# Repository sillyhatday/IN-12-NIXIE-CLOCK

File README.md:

# IN-12 Nixie Tube Clock

## Introduction

This clock was designed with the idea of using IN-12 Nixie Tubes as its display. The design was intended to look similar to something from the 1960s with a cyberpunk style. I'm not sure I have managed this or not. I think it is more art deco style.

This did not work out and I went for something that took inspo from the 1950s. I'd say more Fallout than cyberpunk. Maybe American diner or 50's American car. I like it.

The design is to be modular and 3D printing or machining friendly. The final build I would like making from aluminium or stainless steel.

---

## 🔷 Description

The internal electronics are mounted on two PCBs with a connecting pin header. One PCB for power supplies and main logic, the second for the displays and display driver. The choice of putting the display driver on the display PCB was to reduce the amount board to board connections.

The clock housing is keyed to the cut outs in the PCBs. It's not possible to put them in the wron gplace.

The logic board contains two power supplies. One power supply is for the display tube anodes. The second power supply provides power to the logic circuit.

A 9 - 12v DC supply was decided based on testing. The system will operate from 8 to 16v on the input. I have been running mine at 9v as that is supported by more USB C power supplies than 12v.

>[!NOTE]
>Before building, decide if you will use NiMH or Alkaline batteries for backup batteries. If using non-rechargable, do not populate R39 <br>
>I suggest using the ATmega328 over the ATmega8 for lower standby power and longer operation on backup batteries. <br>
>A description of operations can be found [HERE](ClockFunctions.md)

---

## 🫐 Progress

### 🟢 Done
- First revision of PCBs
- Working firmware with some features implemented.
- Stable high voltage power supply
- Case design first revision made
- All remaining case parts, buttons, legs, back cover.
- Updated PCB & fixed errors. Changed fuse, standby circuit, rearranged PCB.
- Added onboard USB-C 9 - 12v support.
- Finished adding firmware features, standby, battery backup, EEPROM clear.
- Porting to ATMEGA328 to use lower voltage and more efficient core, LOD 1.8v vs LOD 2.7v.
- Finishing case cosmetics.
- Digit ghosting fix. Problem in hardware somewhere.
- Standby code needs inverting for new 180v power control circuit.

### 🟡 Working On
- Power measurement testing. MCU power reduction on battery power.
- Tidying up lettering on the back.
- New photos of finished product and new PCBs
- LCSC or Mouser cart ready to buy.

### ⚪ Next
- Create prebuild mouser cart

---

## Photos

>[!TIP]
>Some build images can be seen [here](https://github.com/sillyhatday/IN-12-NIXIE-CLOCK/blob/main/CONCEPT%26BUILD.md)

### Complete

>[!NOTE]
>IV-6 Clock project on top. To be broken for parts for something better.

### Final PCB

---

## Complete Parts List

| Part | Part No | Qty |
| --- | --- | --- |
| JST Connector | - | 1 |
| Capacitor | 100nF | 5 |
| Capacitor | 20pF | 2 |
| Capacitor | 1nF | 1 |
| Capacitor | 220pF | 1 |
| Capacitor | 4.7uF | 1 |
| Capacitor | 100uF | 4 |
| Diode | 1N5819 | 4 |
| Diode | UF4007 | 1 |
| Fuse | 300mA | 1 |
| Pin Header | 1x2 | 1 |
| Pin Header | 1x16 | 1 |
| Pin Socket | 1x16 | 1 |
| Inductor | 100uH | 1 |
| Inductor | 220uH | 1 |
| Inductor | 1uH | 1 |
| Transistor | BC516 1 |
| Transistor | KSP92 | 6 |
| Transistor | MPSA42 | 6 |
| Transistor | 2N3904 | 1 |
| MOSFET | IRF9540N | 1 |
| MOSFET | IRF740 | 1 |
| Resistor | 0R75 | 1 |
| Resistor | 0R1 | 1 |
| Resistor | 10K | 21 |
| Resistor | 412K | 6 |
| Resistor | 1K | 5 |
| Resistor | 15K | 1 |
| Resistor | 4K7 | 1 |
| Resistor | 100K | 1 |
| Resistor | 6K8 | 1 |
| Resistor | 1K5 | 2 |
| Resistor | 220K | 1 |
| Potentiometer | 2K | 1 |
| Potentiometer | 1K | 1 |
| Button | SHOU HAN 5.8 WSPT | 4 |
| Button | SHOU HAN 5.8 WSPT | 1 |
| MCU | ATMEGA8 | 1 |
| IC | MC34063A | 2 |
| IC | K155ID1 | 1 |
| Tube | IN-12 Nixie | 6 |
| Crystal | 1MHz | 1 |

---

## 💻 Firmware Changelog

| Version | Status | Notes |
| ------- | ------ | ----- |
| V1.0.0  | Initial | A generally functioning clock. 6 Digits for hours, minutes and seconds. 24 hour mode only. Flashing colon function in time with seconds changing. Reset button to clear contents of hours, minutes and seconds counters. Runs on ATmega8A and Atmega328P at 16MHz external crystal |
| V1.1.0  | Defunct | Fixed bug with hours counter not resetting properly when reset button pressed. Didn't clear hours count. Fixed bug with hours being able to go past 23 when using hours button. Incorrect modulo math |
| V1.2.0  | Defunct | 12 hour time mode added. Selectable with button. Keeps time when switching to 12 hour mode only |
| V1.3.0  | Defunct | 12 hour mode improved. No longer screwing with the hours counter. Leaving that counter alone and translating the 24 hour format on the fly. Now keeps time switching back and forth between 12/24h modes. Added display function to show what hour mode the system has been switched to. Display routine for showing the hour mode written from scratch due to brightness increase when multiplexing 2 digits vs 6 |
| V1.3.1  | Defunct | Fixed a bug caused by adding 12 hour mode functionality where in normal operation, the time doesn't wrap at 24 back to 0 |
| V1.4.0  | Defunct | Added battery backup mode to disable the MCU trying to display digits on the Nixies when 12v input is removed. Hope to save some power for running on battery power |
| V1.4.5  | Defunct | Updated the dev board to bring all features back in the code. Testing required. Moved button logic into one function. Now it is called from main |
| V1.5.0  | Defunct | Added counter for number of hours clock has been running in total. Display mode triggered when button is pressed. Hijacked the reset button for development. Run time is saved into EEPROM at addresses 0, 1, 2, 3 for unsigned long. Routine runs once. With new MCU addresses are cleared at boot and flag set in address 4 to indicate the EEPROM addresses are initialised. On boot the flag is checked, so as not to overwrite the runtime count |
V1.5.1-1.5.4 | Defunct | Various different attempts at solving the syncing issue of the colon with the seconds tick. The bug appeared after more testing. Removed ISR function that was tried in attempt to keep things in sync and in phase. Rewrote entire colon handling from scratch. Modified timer function to count 500mS ticks to use as reference for colon. Two ticks now count 1 second. Used GPIO pin to control blanking of CD4511 outputs. Removed long complex routine for multiplexing 2 digits. Reduced down to an if statement in main multiplex |
| V1.6.0  | Defunct | Added back in second multiplex routine but inside the main multiplex behind an if statement. Can't recall why I had to add it back in. Must have been buggy. At least it's more stream lined than before. Improved speed of multiplex function by tracking which digit was last displayed and only blanking that one, not all six. Huge improvement to the display crispness. Blanking just one digit saves 83% of the time it took to blank 6 digits. 5 of those did not need to be. Used digitalWriteFast library as a stop gap to using direct port manipulation much later on |
| V1.6.1  | Defunct | General tidy up of formatting. Added lots of comments and removed most comments from each line unless needed for clarity. Most comments are in the top of each function in one text block. Removed some unused variables. Removed reset button references ready to trigger reset on mode button hold, or status hold |
| V1.6.5  | Defunct | Once again removed the second multiplex function for two digit mode. No longer using any digitalWriteFast in multiplex function. Blanking digits with invalid data sent to the CD4511. This was tried before and didn't work as I didn't remember to expand the array for the new data to send. It was sending random data in RAM at that moment instead! This was needed realising that the nixie tube driver doe not have a blanking input. Nixie PSU gate control output added ready for prototype PSU and logic PCB |
| V1.7.0 | Defunct | Removed some debugging code using GPIO pins. Added an output to drive a MOSFET gate that will control the 180v boost supply, depending on 12v input being present or not. Code was added onto the section controlling display blanking as the input to perform the display blanking was already implemented |
| V1.7.1 | Defunct | Changed setup function to deal with stored EEPROM data differently and how it is initialised on first power up. Added in a basic check routine to confirm EEPROM is working, else show 999,999 on the run time display. Not sure it was needed as the problems I was having went away when shifting the EEPROM storage addresses. I think this unknown Aliexpress chip is somewhat dodgy. It is probably worn out. The chip has been reprinted on top while the underside is beat to hell |
| V1.8.0 | Defunct | Implemented a multi-function button routine. Status button now serves dual function. It is a new function in code that handles just that button, where it should be merged with the existing button handler. I don't plan on any more multi function buttons, so I'll leave this alone. Holding the status button now does a software reset of the time. Pressing the button works as before but activates on release of the button, not on the press |
| V1.8.1 | Defunct | Fixed a bug that caused the run time counter to roll over at 255 |
| V2.0.0 | Defunct | Complete rewrite of the whole software. Code is built around state machines now, no more blocking flag everywhere. Some features have been removed or not yet implemented. Missing code for standby function. Removed blinking colon, don't like it anymore |
| V2.1.0 | Defunct | Code modified to work on the real nixie tube setup. Only small things like the multiplex scan direction and stuff I've forgotten. Fixed bug with button debouncing not working great since the re-write. Attempted to fix problem with run time hours data getting messed up. Not wure why as it didnt have any issue on the dev board |
| V2.2.0 | Defunct | Added standby feature back to system. Power loss or power switch perform the same function. Displays off, 180v supply off, sleep cpu. CPU wakes once per second to keep time and check if escape standby. Not sure eeprom fix is working still. Need to add code to stop eeprom code being updated while in sleep. It's only to track tube run time |
| V2.2.3 | Current | Moved software over to ATmega328. Implemented clock divider to reduce clock speed to 2MHz. At 1MHz there was a slight percievable flicker when seconds incremented |

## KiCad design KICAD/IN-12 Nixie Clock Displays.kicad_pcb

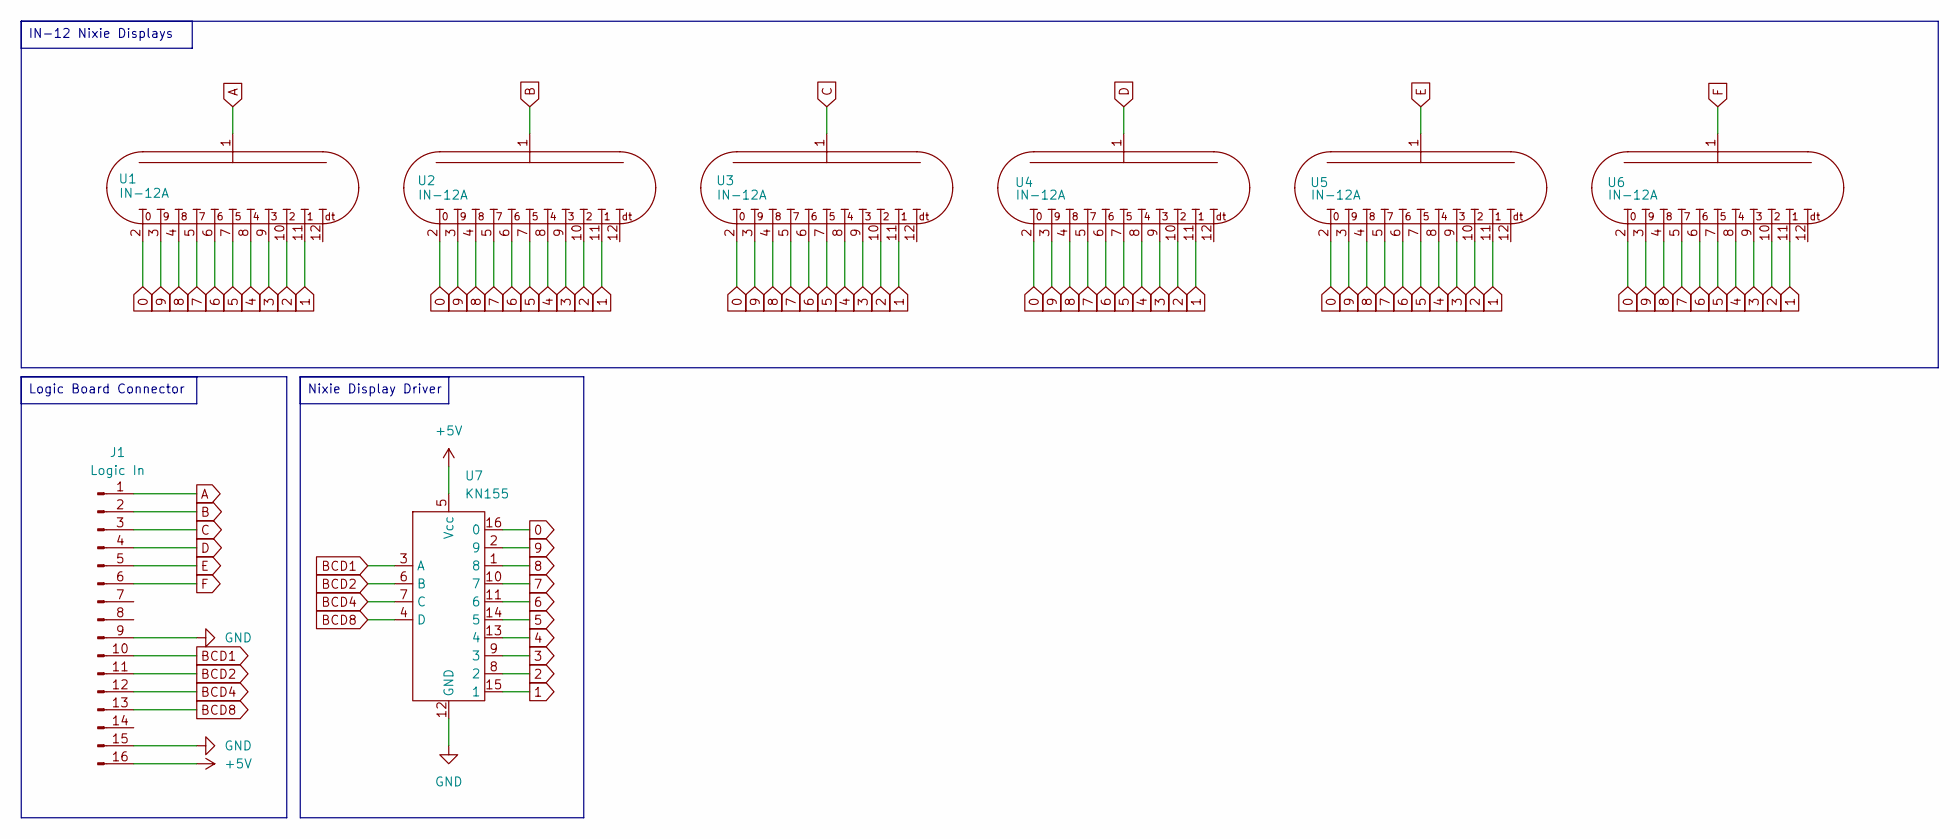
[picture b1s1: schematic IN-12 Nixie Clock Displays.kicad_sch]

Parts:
J1: Logic In; PinHeader_1x16_P2.54mm_Vertical
U1, U2, U3, U4, U5, U6: IN-12A; IN-12
U7: KN155; DIP-16_W7.62mm_Socket

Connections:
0: U1.2, U2.2, U3.2, U4.2, U5.2, U6.2, U7.16 (0)
1: U1.11, U2.11, U3.11, U4.11, U5.11, U6.11, U7.15 (1)
2: U1.10, U2.10, U3.10, U4.10, U5.10, U6.10, U7.8 (2)
3: U1.9, U2.9, U3.9, U4.9, U5.9, U6.9, U7.9 (3)
4: U1.8, U2.8, U3.8, U4.8, U5.8, U6.8, U7.13 (4)
5: U1.7, U2.7, U3.7, U4.7, U5.7, U6.7, U7.14 (5)
6: U1.6, U2.6, U3.6, U4.6, U5.6, U6.6, U7.11 (6)
7: U1.5, U2.5, U3.5, U4.5, U5.5, U6.5, U7.10 (7)
8: U1.4, U2.4, U3.4, U4.4, U5.4, U6.4, U7.1 (8)
9: U1.3, U2.3, U3.3, U4.3, U5.3, U6.3, U7.2 (9)
+5V: J1.16, U7.5 (Vcc)
A: J1.1, U1.1
B: J1.2, U2.1
BCD1: J1.10, U7.3 (A)
BCD2: J1.11, U7.6 (B)
BCD4: J1.12, U7.7 (C)
BCD8: J1.13, U7.4 (D)
C: J1.3, U3.1
D: J1.4, U4.1
E: J1.5, U5.1
F: J1.6, U6.1
GND: J1.9, J1.15, U7.12 (GND)

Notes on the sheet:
IN-12 Nixie Displays
Nixie Display Driver
Logic Board Connector

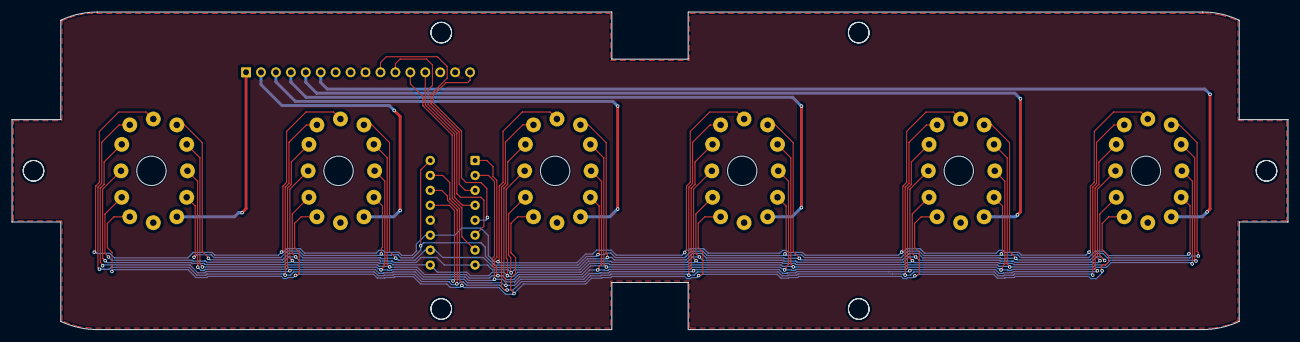
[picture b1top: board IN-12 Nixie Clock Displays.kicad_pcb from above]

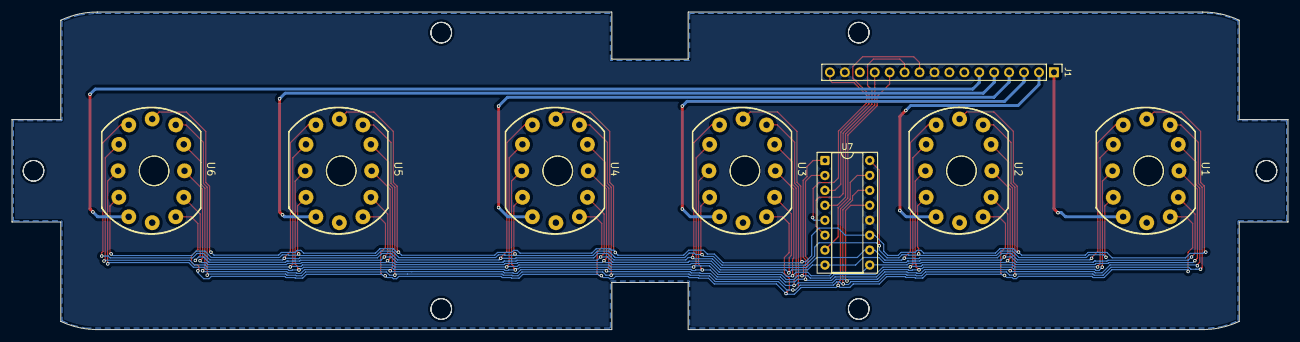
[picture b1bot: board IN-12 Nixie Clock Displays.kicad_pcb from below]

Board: 2 copper layers, 217.0 x 54.0 mm, 8 parts (8 on the bottom side), 22 nets.

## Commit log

2025-10-29 First upload
    firmware version 1.1
2025-10-31 Update README.md
    version 1.3 changelog
2025-10-31 Add files via upload
    backup of code so far. to be organised later
2025-11-02 Update README.md
    added v1.31
2025-11-02 Add files via upload
    version 1.4 - battery backup function
2025-11-03 Update README.md
    added changelog v1.45
2025-11-03 Add files via upload
    version 1.45
2025-11-07 Create firmware-archive.md
    Firmware archive added
2025-11-07 Delete nixie-clock-atmega8-dev-board-firmware-29-10-2025.7z
    organising files
2025-11-07 Delete nixie-clock-atmega8-dev-board-firmware-26-10-2025.7z
    organising files
2025-11-07 Delete nixie-clock-atmega8-dev-board-firmware-27-10-2025.7z
    organising files
2025-11-07 Delete nixie-clock-atmega8-dev-board-firmware-30-10-2025-v1.2.7z
    organising files
2025-11-07 Delete nixie-clock-atmega8-dev-board-firmware-31-10-2025-v1.3.7z
    organising files
2025-11-07 Delete nixie-clock-atmega8-dev-board-firmware-v1.31.7z
    organising files
2025-11-07 Delete nixie-clock-atmega8-dev-board-firmware-v1.4.7z
    organising files
2025-11-07 Delete nixie-clock-atmega8-dev-board-firmware-v1.45.7z
    organising files
2025-11-07 Delete nixie-clock-atmega8-dev-board-firmware.ino
    organising files
2025-11-07 Add files via upload
    reuploaded firmware files
2025-11-09 Update README.md
    version 1.50
2025-11-09 Add files via upload
    version 1.5
2025-11-14 Update README.md
    version 1.54
2025-11-14 Update README.md
    version 1.54 extras
2025-11-14 Add files via upload
    firmware 1.54
2025-11-14 Add files via upload
    1.51 to 1.53
    broken but why not keep em
2025-11-17 Update README.md
    versions 1.6 - 1.61 - 1.65
2025-11-17 Add files via upload
    version 1.6 - 1.61 - 1.65 added
2025-11-17 Update README.md
    updated info in v1.65
2025-11-19 Update README.md
    Major readme update
2025-11-19 Update README.md
    Formatting and pictures
2025-11-19 Update README.md
    heading updated changelog to firmware changelog
2025-11-19 Update README.md
    Explanation of of PCB and housing "keying" and more 3D mock ups added
2025-11-19 Update README.md
    Formatting
2025-11-19 Update README.md
    Resized images
2025-11-25 Update README.md
    Added multiple change logs V1.7 V1.71 V1.8. I think the code for V1.7 has been lost
2025-11-25 Add files via upload
    Added all but missing v1.7
2025-12-09 Update README.md
    v1.81
2025-12-13 Delete firmware directory
    Organising firmware
2025-12-13 Create readme.md
    New directory
2025-12-13 Add files via upload
    Reuploaded firmware
2026-06-04 Update README.md
    Big update
2026-06-04 Create dummy
2026-06-04 Add files via upload
    Current state photos and renders added
2026-06-04 Update README.md
    new photos
2026-06-05 Update README.md
    full bom
2026-06-05 Update README.md
    new renders
2026-06-05 Update README.md
    transistor added to bom
2026-06-07 Update README.md
    Software version updates
2026-06-09 Update README.md
    Updated progress:
    case done
    pcb rev done
    usb c done
    code features done
    started atmega328 port
2026-06-09 Create POWER_USAGE_TESTS.md
    began recording power usage data
2026-06-10 Update POWER_USAGE_TESTS.md
    2mhz results added 2 max power saving options
2026-06-12 Update README.md
    Updated intro to match current progress.
    Updated parts list to be more brief.
    Updated software log to V2.2.3
2026-06-12 Add files via upload
    parts for you
2026-06-12 Update README.md
    added section on battery charging
2026-06-23 Update README.md
    super fast tidy up
2026-06-24 Update POWER_USAGE_TESTS.md
    typo
2026-06-24 Update README.md
    removed clock functions
2026-06-26 Update README.md
    photo updates
